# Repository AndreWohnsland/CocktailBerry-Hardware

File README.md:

<br/>

CocktailBerry Hardware is the **official hardware repository** for the [CocktailBerry](https://github.com/AndreWohnsland/CocktailBerry) project.
It holds the machine designs (FreeCAD sources) and custom PCB(A)s (KiCad projects) you need to build your own CocktailBerry machine.

Build guides, parts lists, specifications, and downloadable fabrication files live in the
**[Hardware Documentation](https://hardware.cocktailberry.org/)**. For the software, setup, and
configuration, see the [main CocktailBerry project](https://github.com/AndreWohnsland/CocktailBerry)
and the [Software Documentation](https://software.cocktailberry.org/).

Like this project? Give the main repo a star on GitHub! ⭐

# Designs

Sources live in this repo; fabrication files (Gerbers/BOM/CPL for boards, STEP/STL for machines)
are generated from them by the build pipeline. Full specs, parts, and downloads are on the
[Hardware Documentation](https://hardware.cocktailberry.org/).

**PCBAs** ([`pcb/`](pcb)) — control boards that replace relay arrays, switching pump circuits via MOSFETs:

| Board                                                                                         | Description                          | Status   |
| --------------------------------------------------------------------------------------------- | ------------------------------------ | -------- |
| [CocktailBerryBoard GPIO](https://hardware.cocktailberry.org/pcbas/cocktailberry-board-gpio/) | GPIO-based, up to 10 circuits        | Released |
| [CocktailBerryBoard Slim](https://hardware.cocktailberry.org/pcbas/cocktailberry-board-slim/) | Compact GPIO-based, up to 8 circuits | Released |
| [CocktailBerryBoard I2C](https://hardware.cocktailberry.org/pcbas/cocktailberry-board-i2c/)   | I2C-based, up to 10 circuits         | Beta     |

**Machines** ([`cad/`](cad)) — 3D-printable machine builds:

| Machine                                                                  | Description                                            | Status   |
| ------------------------------------------------------------------------ | ------------------------------------------------------ | -------- |
| [CocktailBerry MK III](https://hardware.cocktailberry.org/machines/mk3/) | Compact footprint with integrated touchscreen support  | Released |
| [CocktailBerry 2-Go](https://hardware.cocktailberry.org/machines/2-go/)  | Portable Euro Box build with detachable legs           | Released |
| [CocktailBerry MK IV](https://hardware.cocktailberry.org/machines/mk4/)  | v2 reference build, optional scale + peristaltic pumps | Beta     |

# Contributing / How to Help

Contributions are very welcome - a new machine design, an improved model, or a PCB layout.
Open an issue or pull request.

**Please submit source files only:**

- PCBs: the KiCad project (`*.kicad_sch`, `*.kicad_pcb`, and any local symbols/footprints)
- Machines: the FreeCAD sources (`*.FCStd`)

Do **not** commit generated fabrication artifacts (Gerbers, drill, CPL, STL, STEP) - those are
built from the sources by the pipeline (see [`pcb/README.md`](pcb/README.md) and
[`cad/README.md`](cad/README.md)). See the main project's
[Contributing Guidelines](https://github.com/AndreWohnsland/CocktailBerry/blob/master/CONTRIBUTING.md)
for general rules.

# Related Projects

| Project                                                                        | Description                                |
| ------------------------------------------------------------------------------ | ------------------------------------------ |
| [CocktailBerry](https://github.com/AndreWohnsland/CocktailBerry)               | The main software project (Python + React) |
| [CocktailBerry Addons](https://github.com/AndreWohnsland/CocktailBerry-Addons) | Community addons and extensions            |
| [Software Documentation](https://software.cocktailberry.org/)                  | Software setup and configuration guides    |

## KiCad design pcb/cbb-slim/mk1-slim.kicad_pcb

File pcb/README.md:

# PCB

KiCad projects for the CocktailBerry boards (and room for other PCB-related
components later). JLCPCB fabrication files (Gerbers, drill, BOM, CPL) are
generated headlessly - on release by CI, or locally - with
[KiKit](https://github.com/yaqwsx/KiKit) via
[`scripts/build_fab.py`](../scripts/build_fab.py).

## Layout & conventions

```shell
pcb/<board>/
  <board>.kicad_pcb   # exactly one PCB per board folder
  <board>.kicad_sch   # root schematic (shares the project base name)
  *.kicad_sch         # hierarchical sub-sheets (e.g. a reused pump circuit)
  ...                 # symbols/footprints/etc. live alongside as usual
```

- Each board folder must contain **exactly one** `*.kicad_pcb` (one layout per
  project, no matter how many schematic sheets exist).
- **Hierarchical schematics are fine.** Only the **root** sheet (named after the
  project, like the `.kicad_pcb`) is passed to KiKit; it walks the hierarchy and
  pulls in all sub-sheets - so a pump circuit reused 10× flattens into the
  BOM/CPL automatically.
- Components to be assembled need their **LCSC part number** in the `MPN`
  schematic field (see `LCSC_FIELD` in `scripts/build_fab.py`). Parts without it
  appear in the BOM without an LCSC code and won't be placed.

## Running

KiKit + KiCad (`pcbnew`) are **not** uv dependencies; install them separately
(`apt-get install kicad` + `pip install kikit` on CI). Then:

```bash
uv run python scripts/build_fab.py            # all boards -> dist/<board>.zip
uv run python scripts/build_fab.py cbb-gpio    # a single board
```

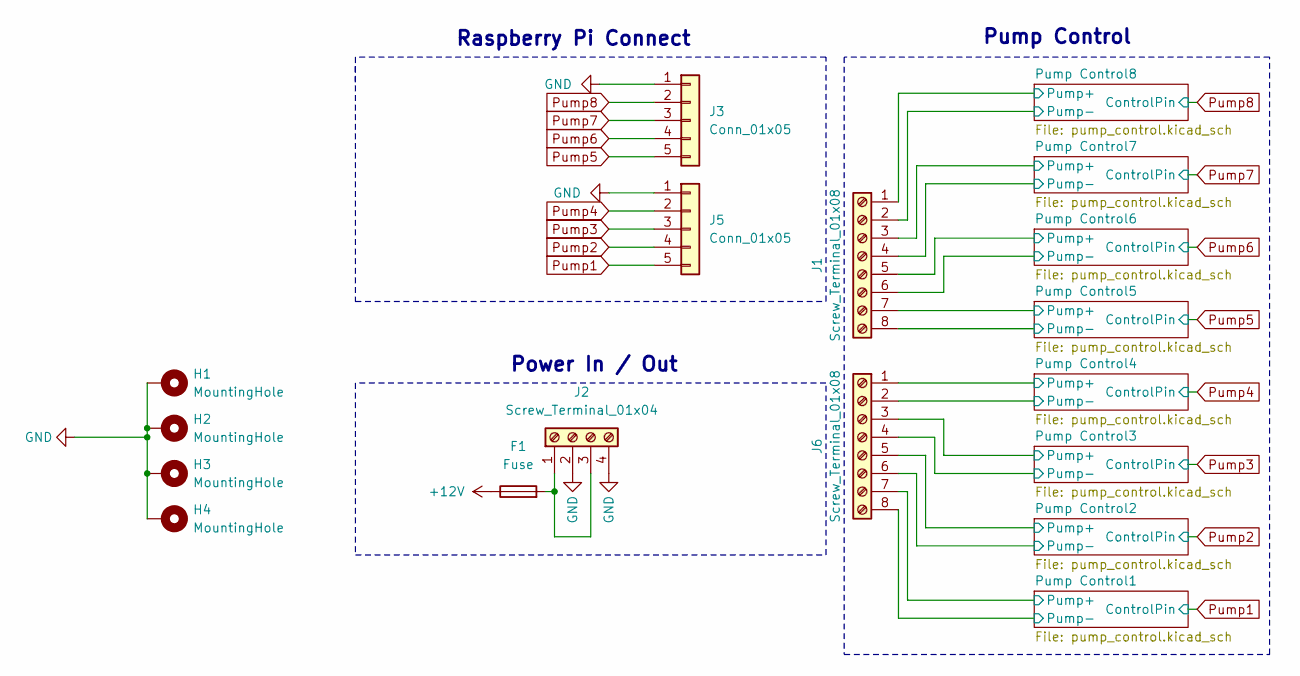
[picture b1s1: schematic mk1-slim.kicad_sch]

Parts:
F1: Fuse; Fuse_Littelfuse_395Series; MPN C22396288
H1, H2, H3, H4: MountingHole; MountingHole_2.7mm_M2.5_ISO7380_Pad
J1, J6: Screw_Terminal_01x08; TerminalBlock_Phoenix_MKDS-1,5-8_1x08_P5.00mm_Horizontal; MPN C430626
J2: Screw_Terminal_01x04; TerminalBlock_Phoenix_MKDS-1,5-4_1x04_P5.00mm_Horizontal; MPN C430624
J3, J5: Conn_01x05; PinSocket_1x05_P2.54mm_Vertical; MPN C124379

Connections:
+12V: F1.1, J1.1, J1.3, J1.5, J1.7, J6.1, J6.3, J6.5, J6.7; also elsewhere on the board
/Pump Control1/Pump-: J6.8; also elsewhere on the board
/Pump Control2/Pump-: J6.6; also elsewhere on the board
/Pump Control3/Pump-: J6.4; also elsewhere on the board
/Pump Control4/Pump-: J6.2; also elsewhere on the board
/Pump Control5/Pump-: J1.8; also elsewhere on the board
/Pump Control6/Pump-: J1.6; also elsewhere on the board
/Pump Control7/Pump-: J1.4; also elsewhere on the board
/Pump Control8/Pump-: J1.2; also elsewhere on the board
GND: H1.1, H2.1, H3.1, H4.1, J2.2, J2.4, J3.1, J5.1; also elsewhere on the board
unnamed: F1.2, J2.1, J2.3
Pump1: J5.5; also elsewhere on the board
Pump2: J5.4; also elsewhere on the board
Pump3: J5.3; also elsewhere on the board
Pump4: J5.2; also elsewhere on the board
Pump5: J3.5; also elsewhere on the board
Pump6: J3.4; also elsewhere on the board
Pump7: J3.3; also elsewhere on the board
Pump8: J3.2; also elsewhere on the board

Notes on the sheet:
Pump Control
Raspberry Pi Connect
Power In / Out

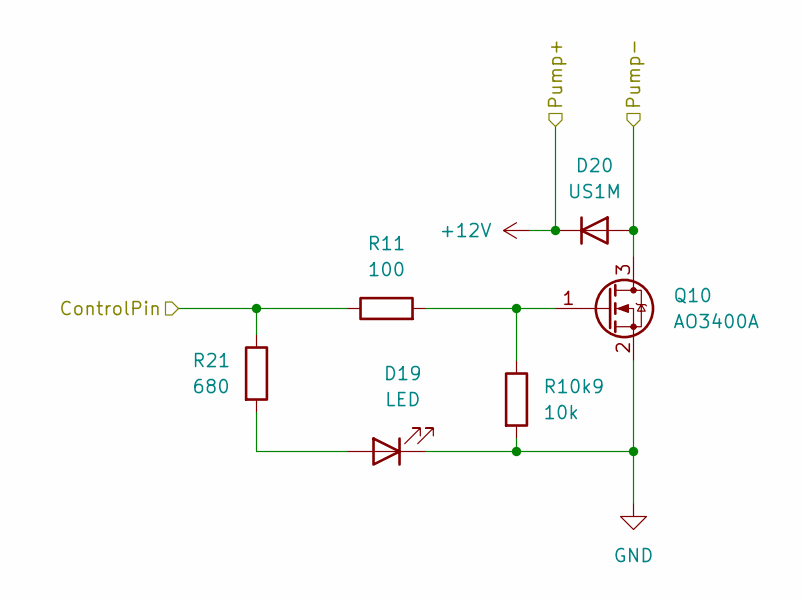
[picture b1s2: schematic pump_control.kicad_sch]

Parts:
D19: LED; LED_0603_1608Metric; mpn C2286
D20: US1M; D_SMA; mpn C412437
Q10: AO3400A; SOT-23; mpn C20917
R10k9: 10k; R_0603_1608Metric; mpn C25804
R11: 100; R_0603_1608Metric; mpn C22775
R21: 680; R_0603_1608Metric; mpn C23228

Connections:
+12V: D20.1 (K); also elsewhere on the board
/Pump Control1/Pump-: D20.2 (A), Q10.3 (D); also elsewhere on the board
GND: D19.1 (K), Q10.2 (S), R10k9.2; also elsewhere on the board
unnamed: D19.2 (A), R21.2
unnamed: Q10.1 (G), R10k9.1, R11.2
Pump1: R11.1, R21.1; also elsewhere on the board

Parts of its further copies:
D1, D3, D5, D11, D13, D15, D17: LED; LED_0603_1608Metric; mpn C2286
D2, D4, D6, D12, D14, D16, D18: US1M; D_SMA; mpn C412437
Q1, Q2, Q3, Q6, Q7, Q8, Q9: AO3400A; SOT-23; mpn C20917
R1, R3, R4, R7, R8, R9, R10: 100; R_0603_1608Metric; mpn C22775
R2, R10k1, R10k2, R10k5, R10k6, R10k7, R10k8: 10k; R_0603_1608Metric; mpn C25804

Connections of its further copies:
+12V: D2.1 (K), D4.1 (K), D6.1 (K), D12.1 (K), D14.1 (K), D16.1 (K), D18.1 (K); also elsewhere on the board
/Pump Control2/Pump-: D18.2 (A), Q9.3 (D); also elsewhere on the board
/Pump Control3/Pump-: D16.2 (A), Q8.3 (D); also elsewhere on the board
/Pump Control4/Pump-: D14.2 (A), Q7.3 (D); also elsewhere on the board
/Pump Control5/Pump-: D12.2 (A), Q6.3 (D); also elsewhere on the board
/Pump Control6/Pump-: D2.2 (A), Q1.3 (D); also elsewhere on the board
/Pump Control7/Pump-: D4.2 (A), Q2.3 (D); also elsewhere on the board
/Pump Control8/Pump-: D6.2 (A), Q3.3 (D); also elsewhere on the board
GND: D1.1 (K), D3.1 (K), D5.1 (K), D11.1 (K), D13.1 (K), D15.1 (K), D17.1 (K), Q1.2 (S), Q2.2 (S), Q3.2 (S), Q6.2 (S), Q7.2 (S), Q8.2 (S), Q9.2 (S), R2.2, R10k1.2, R10k2.2, R10k5.2, R10k6.2, R10k7.2, R10k8.2; also elsewhere on the board
unnamed 10: D1.2 (A); also elsewhere on the board
unnamed 11: D3.2 (A); also elsewhere on the board
unnamed 12: D5.2 (A); also elsewhere on the board
unnamed 13: D11.2 (A); also elsewhere on the board
unnamed 14: D13.2 (A); also elsewhere on the board
unnamed 15: D15.2 (A); also elsewhere on the board
unnamed 16: D17.2 (A); also elsewhere on the board
unnamed: Q1.1 (G), R1.2, R2.1
unnamed: Q2.1 (G), R3.2, R10k1.1
unnamed: Q3.1 (G), R4.2, R10k2.1
unnamed: Q6.1 (G), R7.2, R10k5.1
unnamed: Q7.1 (G), R8.2, R10k6.1
unnamed: Q8.1 (G), R9.2, R10k7.1
unnamed: Q9.1 (G), R10.2, R10k8.1
Pump2: R10.1; also elsewhere on the board
Pump3: R9.1; also elsewhere on the board
Pump4: R8.1; also elsewhere on the board
Pump5: R7.1; also elsewhere on the board
Pump6: R1.1; also elsewhere on the board
Pump7: R3.1; also elsewhere on the board
Pump8: R4.1; also elsewhere on the board

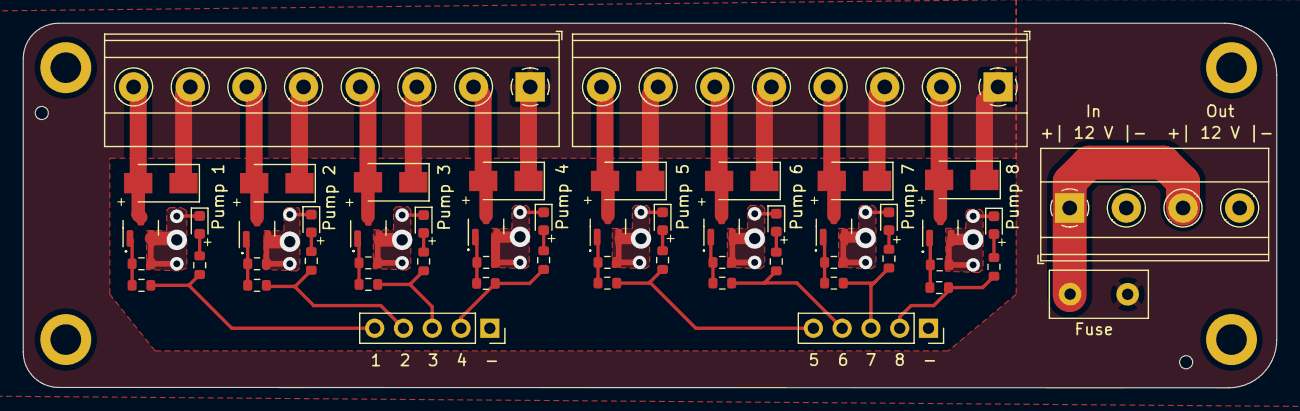
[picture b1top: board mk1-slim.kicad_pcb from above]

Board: 2 copper layers, 110.6 x 32.2 mm, 58 parts (0 on the bottom side), 35 nets.

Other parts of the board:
R12, R13, R14, R17, R18, R19, R20: 220; R_0603_1608Metric

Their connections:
unnamed 10: R12.2; also elsewhere on the board
unnamed 11: R13.2; also elsewhere on the board
unnamed 12: R14.2; also elsewhere on the board
unnamed 13: R17.2; also elsewhere on the board
unnamed 14: R18.2; also elsewhere on the board
unnamed 15: R19.2; also elsewhere on the board
unnamed 16: R20.2; also elsewhere on the board
Pump2: R20.1; also elsewhere on the board
Pump3: R19.1; also elsewhere on the board
Pump4: R18.1; also elsewhere on the board
Pump5: R17.1; also elsewhere on the board
Pump6: R12.1; also elsewhere on the board
Pump7: R13.1; also elsewhere on the board
Pump8: R14.1; also elsewhere on the board

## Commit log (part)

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2026-06-06 add licence
2026-06-07 add base readme
2026-06-09 add base doc files
2026-06-09 fix naming
2026-06-10 start populating mk3 and cbb docs
2026-06-11 add base release pipeline
2026-06-16 first bodies test
2026-06-17 adjust freecad build steps
2026-06-17 optimize cicd outputs
2026-06-17 fix part naming
2026-06-17 add cad parameters
2026-06-17 add cocktailberry board gpio
2026-06-17 exclude parameters from build
2026-06-17 ignore backups
2026-06-17 add build optimization
2026-06-17 add correction file
2026-06-18 split manual build artifacts
2026-06-21 extend base skeletons for machines
2026-06-21 base docs and files for mk3
2026-06-23 add mk3 gpio recommendation
2026-06-25 Finalize mk3
2026-06-25 update cbb gpio
2026-06-25 add screws to mk3
2026-06-25 adjust shared docs section
2026-06-25 adjust pcb git
2026-06-26 add 2-go parts
2026-06-26 add build instructions for 2go
2026-06-26 restructure docs folder naming
2026-06-26 streamlined docs hyphens
2026-06-27 add docs for available pcbas
2026-06-27 add slim CBB
2026-06-27 combine 2go bodies
2026-06-28 adjust mk4 needed parts
2026-06-28 exclude shared folders for fab toolkit
2026-06-29 add first assembly image to mk4
